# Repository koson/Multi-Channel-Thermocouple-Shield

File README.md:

# Multi-Channel-Thermocouple-Shield
Multi Channel Thermocouple Shield MAX6675

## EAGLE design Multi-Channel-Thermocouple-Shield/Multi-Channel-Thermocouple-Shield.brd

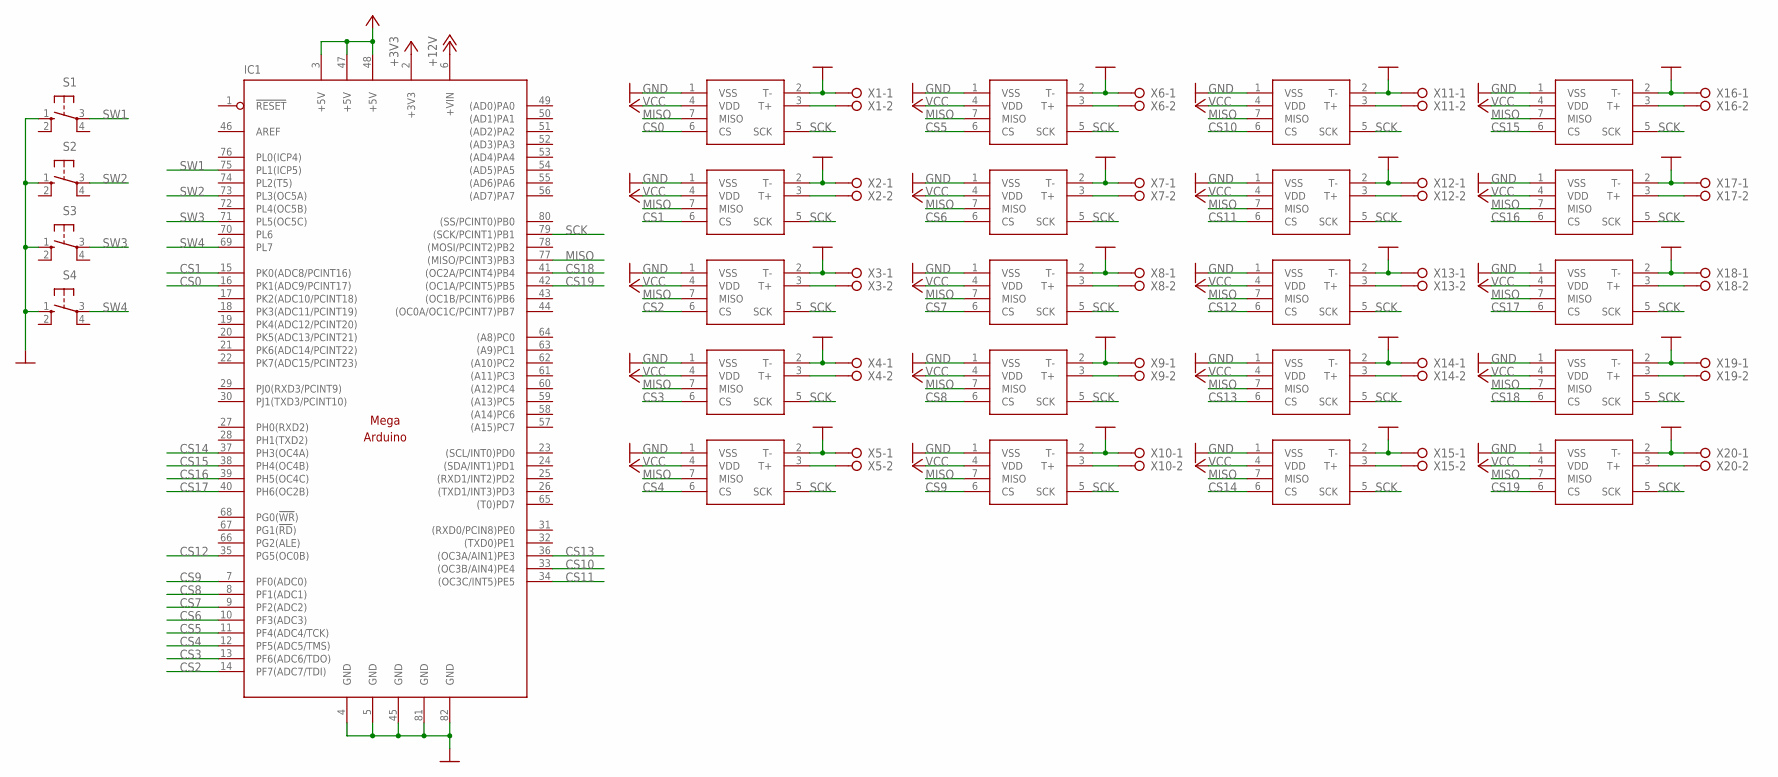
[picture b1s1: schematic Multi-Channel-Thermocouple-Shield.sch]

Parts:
IC1: ARDUINO_MEGA-SHIELD; MEGA_ARDUINO
S1, S2, S3, S4: SW-PUSHBUTTON; B3F-10XX
U$1, U$2, U$3, U$4, U$5, U$6, U$7, U$8, U$9, U$10, U$11, U$12, U$13, U$14, U$15, U$16, U$17, U$18, U$19, U$20: MAX6675; SO08
X1, X2, X3, X4, X5, X6, X7, X8, X9, X10, X11, X12, X13, X14, X15, X16, X17, X18, X19, X20: W237-02P; W237-132

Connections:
+3V3: IC1.2 (+3V3)
+12V: IC1.6 (+VIN)
CS0: IC1.16 (PK1(ADC9/PCINT17)), U$1.6 (CS)
CS1: IC1.15 (PK0(ADC8/PCINT16)), U$2.6 (CS)
CS2: IC1.14 (PF7(ADC7/TDI)), U$3.6 (CS)
CS3: IC1.13 (PF6(ADC6/TDO)), U$4.6 (CS)
CS4: IC1.12 (PF5(ADC5/TMS)), U$5.6 (CS)
CS5: IC1.11 (PF4(ADC4/TCK)), U$6.6 (CS)
CS6: IC1.10 (PF3(ADC3)), U$7.6 (CS)
CS7: IC1.9 (PF2(ADC2)), U$8.6 (CS)
CS8: IC1.8 (PF1(ADC1)), U$9.6 (CS)
CS9: IC1.7 (PF0(ADC0)), U$10.6 (CS)
CS10: IC1.33 ((OC3B/AIN4)PE4), U$11.6 (CS)
CS11: IC1.34 ((OC3C/INT5)PE5), U$12.6 (CS)
CS12: IC1.35 (PG5(OC0B)), U$13.6 (CS)
CS13: IC1.36 ((OC3A/AIN1)PE3), U$14.6 (CS)
CS14: IC1.37 (PH3(OC4A)), U$15.6 (CS)
CS15: IC1.38 (PH4(OC4B)), U$16.6 (CS)
CS16: IC1.39 (PH5(OC4C)), U$17.6 (CS)
CS17: IC1.40 (PH6(OC2B)), U$18.6 (CS)
CS18: IC1.41 ((OC2A/PCINT4)PB4), U$19.6 (CS)
CS19: IC1.42 ((OC1A/PCINT5)PB5), U$20.6 (CS)
GND: IC1.4 (GND), IC1.5 (GND), IC1.45 (GND), IC1.81 (GND), IC1.82 (GND), S1.1 (S), S2.1 (S), S3.1 (S), S4.1 (S), U$1.1 (VSS), U$1.2 (T-), U$2.1 (VSS), U$2.2 (T-), U$3.1 (VSS), U$3.2 (T-), U$4.1 (VSS), U$4.2 (T-), U$5.1 (VSS), U$5.2 (T-), U$6.1 (VSS), U$6.2 (T-), U$7.1 (VSS), U$7.2 (T-), U$8.1 (VSS), U$8.2 (T-), U$9.1 (VSS), U$9.2 (T-), U$10.1 (VSS), U$10.2 (T-), U$11.1 (VSS), U$11.2 (T-), U$12.1 (VSS), U$12.2 (T-), U$13.1 (VSS), U$13.2 (T-), U$14.1 (VSS), U$14.2 (T-), U$15.1 (VSS), U$15.2 (T-), U$16.1 (VSS), U$16.2 (T-), U$17.1 (VSS), U$17.2 (T-), U$18.1 (VSS), U$18.2 (T-), U$19.1 (VSS), U$19.2 (T-), U$20.1 (VSS), U$20.2 (T-), X1.1, X2.1, X3.1, X4.1, X5.1, X6.1, X7.1, X8.1, X9.1, X10.1, X11.1, X12.1, X13.1, X14.1, X15.1, X16.1, X17.1, X18.1, X19.1, X20.1
MISO: IC1.77 ((MISO/PCINT3)PB3), U$1.7 (MISO), U$2.7 (MISO), U$3.7 (MISO), U$4.7 (MISO), U$5.7 (MISO), U$6.7 (MISO), U$7.7 (MISO), U$8.7 (MISO), U$9.7 (MISO), U$10.7 (MISO), U$11.7 (MISO), U$12.7 (MISO), U$13.7 (MISO), U$14.7 (MISO), U$15.7 (MISO), U$16.7 (MISO), U$17.7 (MISO), U$18.7 (MISO), U$19.7 (MISO), U$20.7 (MISO)
unnamed: U$10.3 (T+), X10.2
unnamed: U$1.3 (T+), X1.2
unnamed: U$2.3 (T+), X2.2
unnamed: U$3.3 (T+), X3.2
unnamed: U$4.3 (T+), X4.2
unnamed: U$5.3 (T+), X5.2
unnamed: U$6.3 (T+), X6.2
unnamed: U$7.3 (T+), X7.2
unnamed: U$8.3 (T+), X8.2
unnamed: U$9.3 (T+), X9.2
unnamed: U$11.3 (T+), X11.2
unnamed: U$12.3 (T+), X12.2
unnamed: U$13.3 (T+), X13.2
unnamed: U$14.3 (T+), X14.2
unnamed: U$15.3 (T+), X15.2
unnamed: U$16.3 (T+), X16.2
unnamed: U$17.3 (T+), X17.2
unnamed: U$18.3 (T+), X18.2
unnamed: U$19.3 (T+), X19.2
unnamed: U$20.3 (T+), X20.2
SCK: IC1.79 ((SCK/PCINT1)PB1), U$1.5 (SCK), U$2.5 (SCK), U$3.5 (SCK), U$4.5 (SCK), U$5.5 (SCK), U$6.5 (SCK), U$7.5 (SCK), U$8.5 (SCK), U$9.5 (SCK), U$10.5 (SCK), U$11.5 (SCK), U$12.5 (SCK), U$13.5 (SCK), U$14.5 (SCK), U$15.5 (SCK), U$16.5 (SCK), U$17.5 (SCK), U$18.5 (SCK), U$19.5 (SCK), U$20.5 (SCK)
SW1: IC1.75 (PL1(ICP5)), S1.3
SW2: IC1.73 (PL3(OC5A)), S2.3
SW3: IC1.71 (PL5(OC5C)), S3.3
SW4: IC1.69 (PL7), S4.3
VCC: IC1.3 (+5V), IC1.47 (+5V), IC1.48 (+5V), U$1.4 (VDD), U$2.4 (VDD), U$3.4 (VDD), U$4.4 (VDD), U$5.4 (VDD), U$6.4 (VDD), U$7.4 (VDD), U$8.4 (VDD), U$9.4 (VDD), U$10.4 (VDD), U$11.4 (VDD), U$12.4 (VDD), U$13.4 (VDD), U$14.4 (VDD), U$15.4 (VDD), U$16.4 (VDD), U$17.4 (VDD), U$18.4 (VDD), U$19.4 (VDD), U$20.4 (VDD)

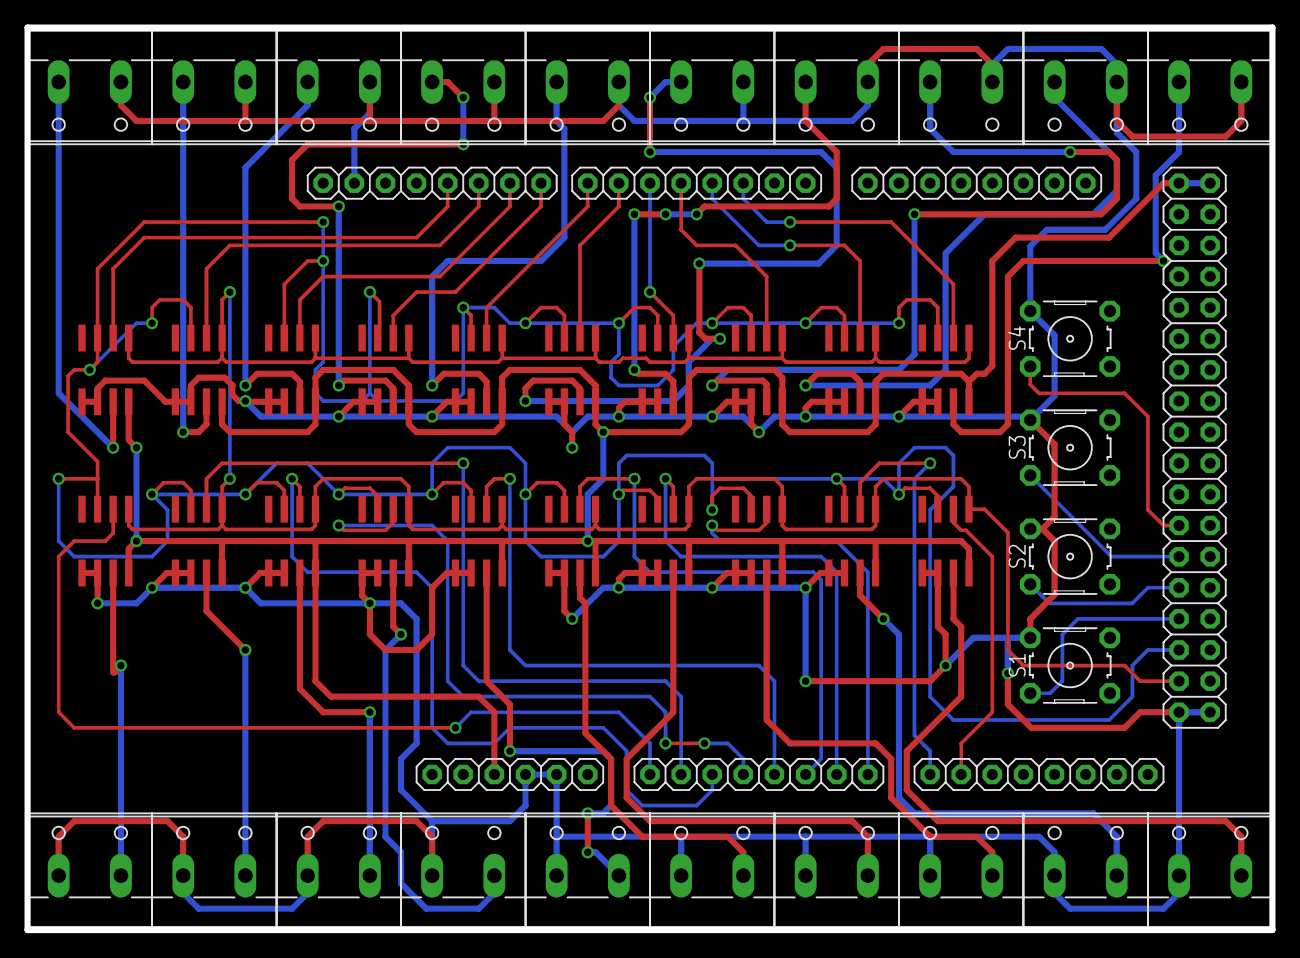
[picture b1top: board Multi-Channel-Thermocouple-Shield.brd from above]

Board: 2 copper layers, 101.6 x 73.7 mm, 45 parts (0 on the bottom side), 48 nets.

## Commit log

2017-10-03 Added HW Design Files
2023-02-24 add kicad
2024-04-09 kicad
